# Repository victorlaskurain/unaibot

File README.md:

# Unaibot #

This project  is a  remote controller for  any robot  with independent
propulsion for the  left and right wheels: most  tricycle style robots
or any caterpillar robot, among others.

The code is currently being use to remotely control a robot build
around the
[Merkur Toys robot chassis 01](http://eshop.merkureducation.cz/show_product/?id=QuLuudfk8g).

I started  the project with a  double objective. In the  first place I
wanted  to  build a  remote  controlled  robot  for my  children.  The
secondary   objective  was   learning   a  little   bit  about   (AVR)
microcontroller programming. It's  been published in the  hope that it
will be  a good  starting point  for people sharing  any of  these two
goals.

## About this file ##

This file is expected  to be useful as a guide to  the code for anyone
willing to understand  how the whole setup works and  how to customize
it.

## How to build ##

The recommended  way to build  the project is  to execute make  in the
directory where the makefile is located.

```
make
```

This will create  a build directory alongside the  makefile which will
contain all the built files, both  the final binaries and the temporal
artifacts.

### About the build system ###

The  top  level  makefile  is a  non-recursive  makefile.   Using  the
utilities  provided by  the  top level  makefile  defining modules  is
straightforward.  A  module can  be  either  a  static library  or  an
executable:

Defining a module requires three steps:

1. Create a directory for the module, for example `registers`.
2. Put  the source files  in the directory. It  is advised to  put the
   header files in a a subdirectory lik `registers/include`.
3. Add   the   module.mk   module  definition   file,  in   this  case
   `registers/module.mk`.

All the  module definition files  are pretty much alike.  For example,
this is the module definition for the `registers` module:

```make
local_src  := $(wildcard $(src_subdirectory)/*.cpp)
$(call make-library, $(subdirectory)/libshift_register.a, $(local_src))
```

The first line stores  the list of all the source  files of the module
in  a  variable. `src_subdirectory`  is  a  handy make  function  that
returns the source directory.

The second line adds the  library `libshift_register.a` to the list of
libraries to  build.  Make  will use  the source  files listed  in the
variable `local_src`  to build the library.  `subdirectory` is similar
to `src_subdirectory` but  returns the build directory  instead of the
source directory.

The module  definition file for  an executable is very  similar. Let's
take for example the module definition of `robot_main`:

```make
local_src  := $(wildcard $(src_subdirectory)/*.cpp)
$(call make-program, $(subdirectory)/program, $(local_src), command/libcommand.a motor_driver/libmotor_driver.a pwm/libpwm.a shift_register/libshift_register.a serial/libserial.a)
```

As  you  can  see  the  only  noticeable  different  is  the  call  to
`make-program` instead  of `make-library` and the  fact that libraries
on which the program depends must be specified as third parameter.

## High level overview ##

The hardware setup is as follows:

- A smartphone is the remote controller.
- A Raspberry Pi together with an Arduino board make up the controller.
- The chassis is a Merku Toys robot chassis 01.
- Optionally the robot can stream what it sees through a webcam.

This components  form a stack and  communicate with each other  in the
following way:

- The chassis has two motors, one for the left caterpillar and one for
  the right caterpillar.
- The Arduino UNO board controls the motors with a Motor Shield v1 and
  reads commands from the serial port.
- A  Raspberry Pi sends commands  setting motor speeds to  the arduino
  using the serial port and serves  the web that implements the remote
  control.  It  gets remote  commands  through  a websocket.  It  also
  streams the webcam's video through a second websocket.
- The smartphone loads the remote control interface from the Raspberry
  pi, processes user  input and  sends commands  to the  Raspberry via
  websockets. It also renders the video stream if available.

The  user  interface running  on  the  smartphone  is plain  HTML  and
Javascript.

The  implementation of  the  web server  and the  server  side of  the
websockets is Nodejs based.

The code  running on the  Arduino uses the  AVR libraries but  not the
Arduino  libraries. The  reason not  to use  the Arduino  libraries is
twofold:

- Being very high  level and focused on being easy  to use for novices
  they  get in  the way  of  learning how  the microcontroller  really
  works.
- Although this is more a personal opinion rather than a fact based on
  rigorous measurements,  they are not  as type safe and  efficient as
  the might.

The following sections describe the  implementation details of each of
the aforementioned components.

# Motor control #

The motor driver implementation consists of several submodules:

- serial: implementation of a serial  port driver for the HW serial of
  the atmega328p.
- registers: type  safe interface to access the  hardware registers of
  the atmega328p.
- shift_register: implementation of a driver for a 74HCT595N IC.
- command:  implementation of  a command dispatcher.   robot_main uses
  this module to  parse and process the commands read  from the serial
  port  in an  organised  way  (currently there  is  a single  command
  defined so this is a bit of an overkill).
- pwm: implementation of the driver for the HW PWM of the atmega328p.
- motor\_driver: implementation  of a controller for  the Motor Shield
  v1. Uses the shift\_register module and the pwm module.
- robot_main: main   program,  uses serial,  command an  motor\_driver
  modules  and  implements  the   main  program  that  the  atmega328p
  executes.

## Serial port driver ##

### Quickstart ###

To use the serial just instantiate one of the available clases:

- `serial_9600`: unbuffered  read and write support at  9600 baud. All
  operations are synchronous, meaning that they take place in the main
  loop busy waiting as necessary.
- `serial_19200`:   unbuffered   read  and  write   support  at  19200
  baud. Same as the previous one, only faster.
- `serial_9600_async`: buffered  read and write support  at 9600 baud.
  All  operations are  asynchronous, meaning  that the  implementation
  uses interrupts. Reading  does not block as long as  the read buffer
  is not  empty. Conversely,  writing does  not block  as long  as the
  write buffer is not full.
- `serial_19200_async`:  buffered  read  and  write  support at  19200
  baud. Same as the previous one, only faster.

These are  just some of  the available  classes. There are  some other
options and more can be constructed on demand (see next section).

Async  versions   are  generally  more  efficient   but  require  more
memory. The memory requiremente derives  from the need to allocate the
buffers and the interruption handling routines.

In all cases parity and stop bits are the hardware's defaults.

The basic operations are:

- `inline uint8_t read()`: read one byte.
- `inline void write(const uint8_t byte)`: write one byte.

There are also versions to read and write whole buffers which could be
more efficient  than a plain  old loop.  There is  also a set  of free
function  templates which  are  the primary  public  interface to  the
serial port classes:

```c++
template <typename Serial>
uint8_t read(Serial &s);

template<typename Serial, typename SizeType>
inline SizeType read(Serial &s, uint8_t *buff, SizeType size);

template<typename Serial, typename SizeType>
inline SizeType read_line(Serial &s, uint8_t *buff, SizeType size,
                          uint8_t mark = '\n');

// write message and wait for enter key
template<typename serial_t>
void wait(serial_t &ser, const char* msg = 0);
```

### Implementation ###

The  serial  port  driver  is  a class  template  with  the  following
signature:

```c++
template<typename SerialSpeed,
         typename SerialReadMode,
         typename SerialWriteMode>
class serial : public SerialReadMode, public SerialWriteMode [...]
```

It  follows a  simple  policy  based design  where  each  of the  type
parameters represents a policy:

- `SerialSpeed`:  initialises the  serial port to  a given  baud rate,
  parity and stop  bit settings. The currently  available options only
  define different  baud rate  settings leaving  parity and  stop bits
  settings to the hardware's defaults.
- `SerialReadMode`: defines how to read bytes from the serial port. It
  can be set to `not_available` to instantiate a write only serial
  port. This could be useful to save some memory.
- `SerialWriteMode`: the  same   as `SerialReadMode`,  only for  write
  operations.

## Type safe and efficient register access ##

The atmega328p  presents all the  control registers and all  the input
and  output registers  mapped in  the memory  space. The  AVR avr/io.h
defines symbolic names for all  the registers as memory addresses. For
example, io.h defines the B io port  (PORTB) as 25h.  In turn the same
file defines each of this port's  bits as plain integers: PORTB0 is 0,
PORTB1 is 1, etc. This is not type safe, nothing prevents accidentally
mixing register PORTB with bit PORTC3, for example.

registers.hpp  defines  different  types  to  represent  each  of  the
registers uses the template class pin\_t to define different types for
each of the pins and tie  them to their respective register types. The
pin\_t template class defines a set  of functions to set and clear the
bits it represents in a safe way.

This is the interface of pin_t:

```c++
template <typename param_port_t, int pin_number>
struct pin_t
{
    typedef param_port_t port_t;
    inline static int offset();
    inline static void set();
    inline static void clear();
    inline static void set_mode_input();
    inline static void set_mode_output();
};
```

Using registers.hpp clearing the bit number 2 of PORTB turns from:

```
PORB &= ~_BV(PORTB2)
```

into the safer and more expressive:

```
PORTB2_t::clear();
```

The first  version is error  prone because if  we forget say  "~", the
compiler  won't complain  at  all  but the  result  won't  be the  one
expected. In other words, writing incorrect  code is very easy and the
compiler won't  help us.  With the  second option  the intent  is more
clear an writing wrong code is harder.

Moreover, the  implementation of  registers.hpp achieves this  with no
computational   cost.  Compiling   with  optimiseations   enabled  the
following two functions produce exactly the same assembler code:

```c++
uint8_t f1()
{
    PORTB |= _BV(PORTB0);
    PORTB &= ~_BV(PORTB0);
    return -1;
}

uint8_t f2()
{
    PORTB0_t::set();
    PORTB0_t::clear();
    return -1;
}
```

## Shift register driver ##

The  shift_register module  implements a  driver for  the the  74HC595
shift register integrated circuit. The API is a single template class:

```c++
template<typename shift_clk,
         typename store_clk,
         typename output_enable,
         typename ds,
         typename bit_field_t,
         size_t bit_field_size = 8 * sizeof(bit_field_t)>
struct shift_register
{
public:
    shift_register();
    ~shift_register();
    bit_field_t data;
    inline void commit(bit_field_t d)
    inline void commit() const
private:
    shift_register(const shift_register&)                  = delete;
    shift_register(shift_register&&)                       = delete;
    shift_register& operator=(const shift_register &other) = delete;
    shift_register& operator=(shift_register &&other)      = delete;
};

```

These are the template's parameters:

- shift\_clk: the  shift clock pin. A raising edge  in this pin shifts
  the existing bits of the shift register and stores a new bit.

- store\_clk:  the store clock pin.  A raising edge in  this ping puts
  the value of the value of the shift register into the store register
  (the parallel output).

- output_enable: if this pin is high then the output pins will assume
  the high impedance - OFF state.

- ds: the  rising edge of the  shift_clk takes the new  value from the
  value present at this pin.

- bit\_field\_t: the  data type used to represent in  memory the value
  of  the shift  register. Any  type should  be usable  as long  as it
  supports the binary and (&) and  shift bits left (<<) operations. In
  practice integer uint8_t has ever been used.

- bit\_field\_size: the number of  bits in bit\_field\_t. It takes the
  right value depending  on the size of bit\_field\_t, no  need to set
  it manually.

shift\_register expects the  pins to be represented  using an instance
of the  pin\_t described in the  previous section so an  example usage
would be the following:

```c++
#include <vla/shift_register.hpp>
#include <stdint.h>

using namespace vla;

int main(void) {
    // define de type and an instance
    shift_register<PORTD4_t/* arduino pin  4 */,
                   PORTB4_t/* arduino pin 12 */,
                   PORTD7_t/* arduino pin  7 */,
                   PORTB0_t/* arduino pin  8 */,
                   uint8_t> r;
    r.data = 0x81; // clear shift register
    r.commit();    // transfer the value to the parallel outuput
    while(true);   // shift register should show 0x81
}

```

## Command processor ##

The command processor  module provides a simple  framework to dispatch
command to handler  functions. In this context the  commands are plain
strings and the handlers have the following signature:

```c++
uint8_t operator()(const char* str)
```

The dispatcher calls each handler in order and until one of them
returns 0.

There is  no provision  to add handlers  dynamically, instead  all the
handlers   must    be   added   at    the   same   time    using   the
```make_command_dispatcher```  which  takes  any  number  of  callable
objects (functors, plain functions, ...) and returns a dispatcher:

```c++
template<typename ...Ts>
command_dispatcher<Ts...> make_command_dispatcher(const Ts&... args)
```

## PWD driver ##

### Quickstart ###

To  use  one of  the  4  PWD pins  supported  instantiate  one of  the
available classes:

-   ```pcpwm_portd6```,   ```pcpwm_portd5```,  ```pcpwm_portb3```   or
  ```pcpwm_portd3```.

For example:

```c++
// instantiate and configure timer
vla::timer0_pcpwm timer0;
timer0.set_clock(vla::clock_source::PRESCALE_1);
// set up PWM on pin d6
vla::pcpwm_portd6 pwm0a(timer0);
// set 50% duty cycle
pwm0a.set_level(UINT8_MAX / 2);
```

The implementation relays  on two templates.  In the  first place, the
```timer_configuration```  template  class   packs  together  the  two
registers used  to configure any  of the  two supported 8  bit timers.
For  example   the  ```timer0_pcpwm```  instantiation  helps   in  the
configuration of the 0 timer by binding together the two timer control
registers (```TCCR0A_t``` and ```TCCR0B_t```)  and the timer mode.  It
also  provides  a method  (```set_clock```)  to  change the  prescaler
(frequency) programmatically.

In  the second  place,  the  ```pwm``` template  class  binds a  timer
configuration  together with  the comparator  register and  the output
pin. This  class takes the  timer type  as template parameter  and the
timer instance  as constructor parameter.  The later's function  is to
ensure  that  the  user  doesn't  try to  use  a  PWM  output  without
configuring the timer first.

## Motor driver ##

This   module   is  an   driver   implementation   for  the   Adafruit
Motor/Stepper/Servo  Shield  for  Arduino.  The  shield  supports  two
stepper motors  or four DC  motors. This  driver supports only  the DC
motor configuration.

The shield uses a shift register  to set the turning direction of each
of the  four motors. The  implementation relays on the  shift register
module to  handle the shift  register and the  PWM module to  set each
motors power level.

The API is pretty straighforward:

```c++
class motor_driver
{
public:
    motor_driver();
    ~motor_driver();
public:
    motor0_t motor0;
    motor1_t motor1;
    motor2_t motor2;
    motor3_t motor3;
};
```

Once  instantiated  each of  the  four  motors  is available  via  the
corresponding  member  variable. The  type  of  each of  these  member
variables is an instantiation of  a class template. The class template
provides the  following public  member functions, which  hopefully are
self explanatory.

```c++
enum class direction_t : uint8_t
{
    IDLE      = 0x00,
    FORWARD   = 0x01,
    BACKWARD  = 0x02,
    STOP      = 0x11,
    FIRST     = IDLE,
    LAST      = STOP
};

void set_direction(direction_t d);
void set_speed(uint8_t s);
```

## Main program ##

The main program simply reads commands  from the serial port using the
serial port driver, parses them using the command dispatcher and sends
the corresponding lower  level commands to the motor  shield using the
motor driver.

```c++
int main()
{
    const auto CMD_BUFFER_SIZE = 64;
    uint8_t cmd_buffer[CMD_BUFFER_SIZE], err_code;
    serial_9600 ser;
    motor_driver motors;
    auto dispatch = make_command_dispatcher(set_speeds_cmd(motors));
    write_line(ser, "READY");
    while(true) {
        read_line(ser, cmd_buffer, CMD_BUFFER_SIZE, '\r');
        err_code = dispatch(reinterpret_cast<const char*>(&cmd_buffer[0]));
        if (SUCCESS == err_code) {
            write_line(ser, "OK");
        } else {
            write(ser, "ERROR ");
            write_line(ser, hex(err_code));
        }
    }
}
```

# Web based remote control #

The  web based  remote control  is  in the  web_control directory.   A
description  of  the  most  significant  contents  of  this  directory
follows:

- `bootstrap.sh`:   shell   script   to   install  all   the  required
  dependencies.

- `install.sh`:  shell script  to install the  remote controller  as a
  systemd service.  Copies  unaibot_web.js file and the  html, lib and
  node_modules  directories  into   `/opt/unaibot`  and  configures  a
  systemd service to run the the server.

- `lib/unaibot.js`:   it's  a   node   module.  Exports   the  UnaiBot
  constructor which takes as parameters the serial port and optionally
  its  configuration.  Instances of  this  object  provide high  level
  interface  for serial  port communication  between the  main program
  running  on the  Arduino  and the  world, in  this  case the  remote
  controller.

- `lib/botcam.js`: it's a node  module. Exports the BotCam constructor
  which takes as  paramenter the name of a video  device. Instances of
  this object provide the means  to start/stop the capture process and
  signal   the  activation/deactivation   of   the   camera  and   the
  availability of new captured frames.

- `unaibot_web.js`:  this is  the main program,  serves the  HTML page
  that  implements   the  remote's   GUI,  handles  the   server  side
  implementation of the remote's  commands and manages the websocket's
  server side.

## User interface ##

The user interface  is a multitouch web page which  shows two vertical
walls, one at each border.  The left war controls the left caterpillar
while the right  bar controls the right one. Pressing  on the top half
of the  bar lets  the caterpillar  run forward  while pressing  on the
bottom half lets it run backward. The round button at the center allow
activating and deactivating the camera.

A  couple  of Javascript  files  implement  touch event  handling  and
client/server communication.

- `api.js`: implementation of the client side of the protocol.

- `main.js`:  touch  event and  video  activation/deactivation   event
  handling.

## Remote API ##

At page  load the browsers opens  a connection to the  command socket.
Automatically reconnects if the connection breaks for any reason.

Two  types of  messages travel  through the  command socket.  The most
common are the requests and their  responses. The server can also send
asynchronous events to the browser.

There is a  second WebSocket endpoint handled by the  same node server
to stream the webcams video.

### Simple query / response protocol ###

The client  sends the request  and receives responses as  JSON encoded
Javascript objects.

The requests have the following properties:

- id: identifies  each request and must be unique  during the lifetime
  of a connection.

- type: identifies  the type of the message which  the server uses for
  message dispatching.

- data: if  the  messages requires  any  more  information  it can  be
  encoded in this property. The type field dictates the interpretation
  of this property.

The responses have the following properties:

- id: identifies each response, the value is equal to the value of the
  id field of the request to which this response answers.

- data:  the response data. The  type of the requests  dictates how to
  interpret this field and whether it is present at all.

### Asynchronous events ###

Asynchronous events  originate at  the server. The  server is  free to
send events  to the client  at any time.  The events are  JSON encoded
Javascript objects with the following properties:

- evt: a string with the event name. The client library triggers a DOM
  event to communicate the event to any interested listeners.

## Webcam streaming ##

[Jsmpeg](https://github.com/phoboslab/jsmpeg) provides  the Javascript
library to  render MPEG1 into a  canvas element. It also  provides the
necessary framework for  transmitting the vide frames  from the server
to the  client live using  websockets as transport. Although  it might
not be the most efficient codec the whole setup is very simple.

Client side, this three lines of Javascript direct the video player to
connect to the the given  websocket address start playback. The player
just sits there waiting for any video frames to render.

```javascript
var canvas = document.getElementById('video-canvas');
var url = 'ws://'+document.location.hostname+':8080/unaibot/cam';
var player = new JSMpeg.Player(url, {canvas: canvas});
```

Server side three different pieces of code work together to stream the
video.

On the first place the streaming process uses ffmpeg to initialize the
video  device,  capture raw  frames  and  encode  then in  the  format
required by Jsmpeg.

On the  second place there  is of course there  is the handler  of the
`/unaibot/cam` websocket endpoint.  Its  work is accepting connections
and broadcasting the video stream to all connected clients.

On the third place, the `botcam.js` module provides a simple interface
to the video capture device tailored to the needs of Jsmpeg. It how to
run ffmpeg encoder with the appropriate parameters. The module exports
a constructor (BotCam) whose instances have two public methods:

- capture(bool): activates the video  capture (true) or deactivates it
  (false).

- isVideoOn: returns true is the video capture is active.

and emit three events:

- videoOff:  notifies that the video  capture is off.  If  the library
  emits this event before the videoOn  event, then that means that the
  capture could not initialized for  whatever reason (no access to the
  device,  wrong ffmpeg  configuration or  any other  reason). If  the
  library emits this event after  a call to `capture(false)` it simply
  means that the capture shutdown process worked. The library can emit
  this event  at any other time,  which usually means that  the webcam
  got disconnected or for some reason the ffmpeg command died.

- videoOn: notifies that the video capture is on.

- data: when the video capture is  on the video data is made available
  to any interested listeners using  by emitting this event. The event
  object is  in the format required  by Jsmpeg so that  the web socket
  just needs to forward it to the remote clients.

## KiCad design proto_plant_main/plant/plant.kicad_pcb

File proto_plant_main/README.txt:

* PUBLIC ADDRESSES

|------------------------+-----------+---------+-----------+------------------------------------------------------------|
| Name                   | Block     | Address | Type      | Description                                                |
|------------------------+-----------+---------+-----------+------------------------------------------------------------|
| Line 1 bag counter     | Registers |    0x21 | [0,65535] |                                                            |
| Line 1 bag counter top | Registers |    0x36 | [0,65535] | if != 0, stop the line when the counter reaches this value |
| Line 1 bag weight      | Registers |    0x3a | [0,50000] | Real weight in gr. (simulated).                            |
| Line 1 bag weight ref  | Registers |    0x38 | [0,50000] | Weight reference in gr.                                    |
| Line 1 grinder control | Registers |    0x32 | [0,255]   | Grinder duty cycle. Only lowest byte meaningful.           |
| Line 1 grinder on      | Coils     |    0xc9 | [0,1]     | 1 if grinder is running. Read only.                        |
| Line 1 main switch     | Registers |    0x34 | [0,255]   | Only low byte used. If true, line is active.               |
| Line 1 oven power      | Registers |    0x30 | [0,3]     | Only two lowest bits are meaningful: off, 3: full power    |
| Line 2 bag counter     | Registers |    0x15 | [0,65535] |                                                            |
| Line 2 bag counter top | Registers |    0x37 | [0,65535] | if != 0, stop the line when the counter reaches this value |
| Line 2 bag weight      | Registers |    0x3b | [0,50000] | Real weight in gr. (simulated).                            |
| Line 2 bag weight ref  | Registers |    0x39 | [0,50000] | Weight reference in gr.                                    |
| Line 2 grinder control | Registers |    0x33 | [0,255]   | Grinder duty cycle. Only lowest byte meaningful.           |
| Line 2 grinder on      | Coils     |    0xca | [0,1]     | 1 if grinder is running. Read only.                        |
| Line 2 main switch     | Registers |    0x35 | [0,255]   | Only low byte used. If true, line is active.               |
| Line 2 oven power      | Registers |    0x31 | [0,3]     | Only two lowest bits are meaningful: off, 3: full power    |
| Silo level             | Registers |    0x00 | [0,1000]  | RO. Silo fill level. 0: empty, 1000: 100% full             |
|------------------------+-----------+---------+-----------+------------------------------------------------------------|

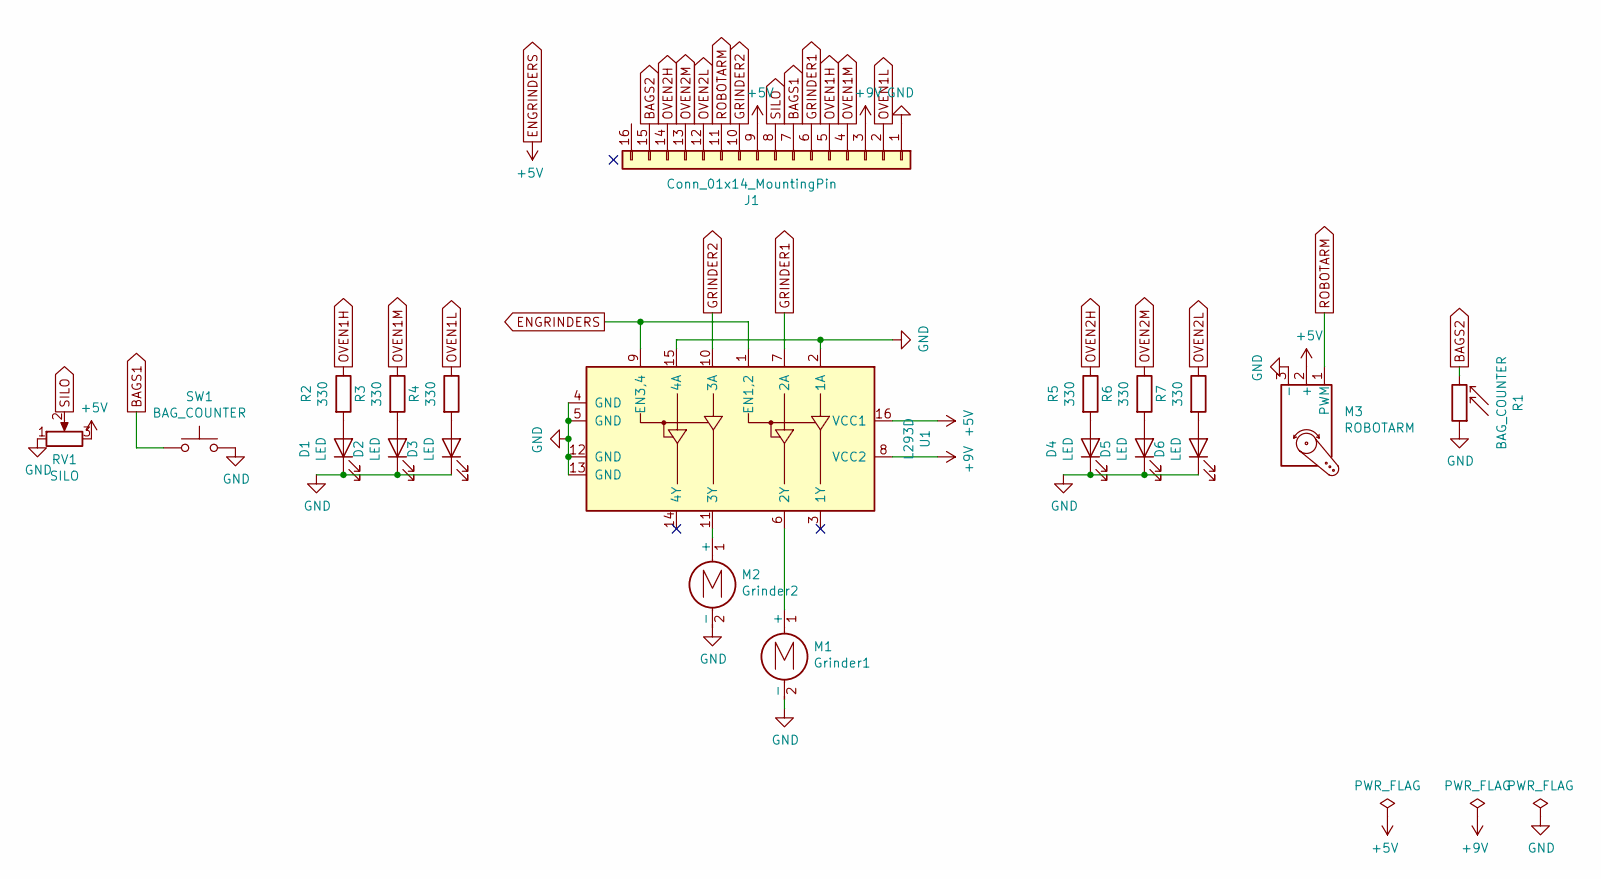
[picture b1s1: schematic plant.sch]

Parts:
D1, D2, D3, D4, D5, D6: LED; LED_D5.0mm
J1: Conn_01x14_MountingPin; PinSocket_1x16_P2.54mm_Vertical
M1: Grinder1; PinHeader_1x02_P2.54mm_Vertical
M2: Grinder2; PinHeader_1x02_P2.54mm_Vertical
M3: ROBOTARM; PinHeader_1x03_P2.54mm_Vertical
R1: BAG_COUNTER; R_LDR_4.9x4.2mm_P2.54mm_Vertical
R2, R3, R4, R5, R6, R7: 330; R_Axial_DIN0204_L3.6mm_D1.6mm_P5.08mm_Horizontal
RV1: SILO; Potentiometer_Bourns_3266Y_Vertical
SW1: BAG_COUNTER; SW_PUSH_6mm_H5mm
U1: L293D; DIP-16_W7.62mm

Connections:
+9V: J1.3, U1.8 (VCC2)
BAGS1: J1.7, SW1.1
BAGS2: J1.15, R1.2
ENGRINDERS: J1.9, M3.2 (+), RV1.3, U1.1 (EN1,2), U1.9 (EN3,4), U1.16 (VCC1)
GND: D1.1 (K), D2.1 (K), D3.1 (K), D4.1 (K), D5.1 (K), D6.1 (K), J1.1, M1.2 (-), M2.2 (-), M3.3 (-), R1.1, RV1.1, SW1.2, U1.2 (1A), U1.4 (GND), U1.5 (GND), U1.12 (GND), U1.13 (GND), U1.15 (4A)
GRINDER1: J1.6, U1.7 (2A)
GRINDER2: J1.10, U1.10 (3A)
unnamed: D1.2 (A), R2.2
unnamed: D2.2 (A), R3.2
unnamed: D3.2 (A), R4.2
unnamed: D4.2 (A), R5.2
unnamed: D5.2 (A), R6.2
unnamed: D6.2 (A), R7.2
unnamed: M1.1 (+), U1.6 (2Y)
unnamed: M2.1 (+), U1.11 (3Y)
OVEN1H: J1.5, R2.1
OVEN1L: J1.2, R4.1
OVEN1M: J1.4, R3.1
OVEN2H: J1.14, R5.1
OVEN2L: J1.12, R7.1
OVEN2M: J1.13, R6.1
ROBOTARM: J1.11, M3.1 (PWM)
SILO: J1.8, RV1.2

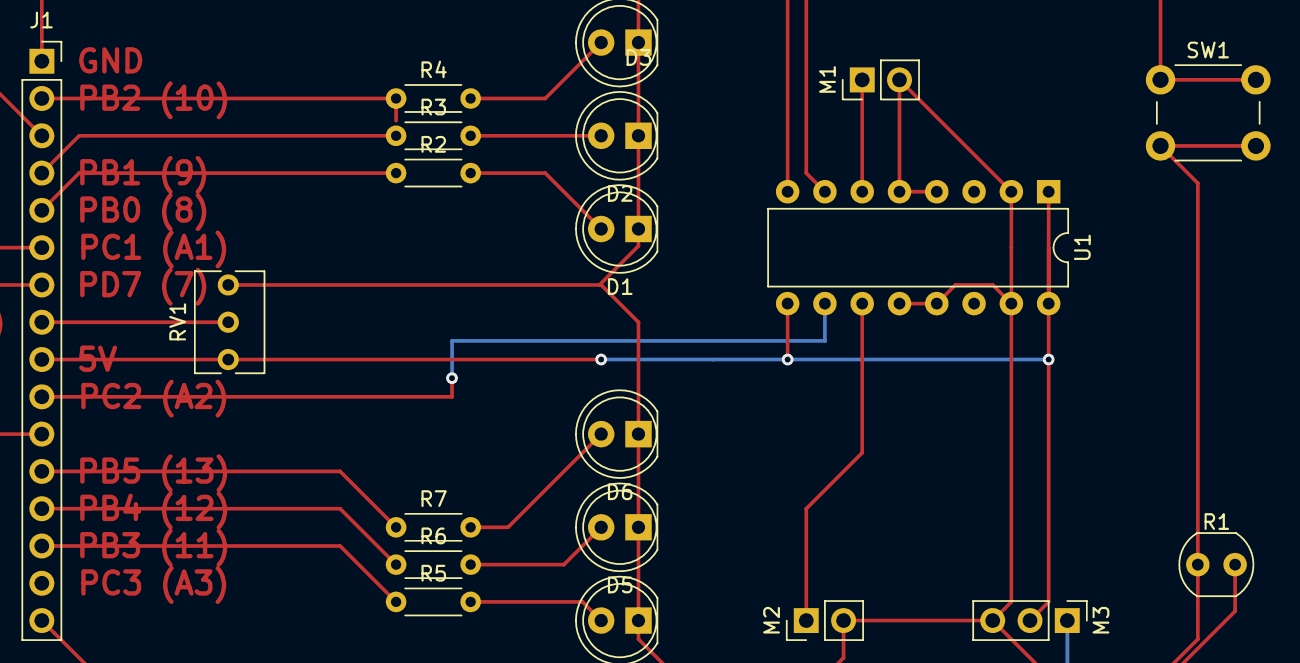
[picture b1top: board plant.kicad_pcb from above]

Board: 2 copper layers, 20 parts (0 on the bottom side), 23 nets.

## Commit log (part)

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2017-01-02 Initial revision.
2017-01-02 Add some comments. Clean up.
2017-01-03 Make less verbose.
2017-01-03 Add wrapper class for phase correct PWD.
2017-01-06 Fix includes.
2017-01-06 Fix comment.
2017-01-06 Add print-and-wait-for-key function for debugging.
2017-01-06 C++ register description.
    The registers module contains hardware register and pin definitions as
    an aid to implement higher level devices. For bit manipulation,
    compiling with optimizations enabled yields the same result as hand
    written bit operations.
2017-01-06 Add template to manage shift registers (74HC_HCT595).
    The test program is configured to switch the pins of the latch of an
    Arduino Motor Shield v1.
2017-01-08 Add compiler guards.
2017-01-08 Add Motor Shield v1 driver.
2017-01-09 Move .hpps to include directory. Use namespace for .hpps.
2017-01-10 Command distpatcher.
2017-01-11 Motor driver program with command dispatcher.
    The program reads commands from the serial line and programs the motor
    shield accordingly. Then reports success or error code back.
2017-01-12 Make STL optional.
2017-01-12 Fix include.
2017-01-12 Don't use strtol in order to save ~500 bytes.
    Reduces de uploaded binary size from 3070 to 2544 by reimplementing
    command parsing using a custom function which reads 0xXX numbers as
    uint8_t.
2017-01-17 Web interface for robot control.
2017-01-18 Extract communication with the arduino to the (new) unaibot module.
    This puts each responsibility where it belongs:
    - unaibot_web.js: handles HTTP and WS requests and dispatches then.
    - unaibot.js: handles serial communication with the arduino and
    provides a nice promise based protocol unaibot_web.
    Also make the serial handshake more solid.
2017-02-04 Systemd config file and install script for the web driver.
2017-02-05 Fix to load unaibot.service at boot.
2017-03-12 Add support for remote webcam.
2017-03-14 Fix visualization of camera feed.
    Change the order of the elements in the index.html to have them stack
    in the right order.
    Set maximum width and height to the canvas.
2017-03-14 Source ffmpeg configuration if needed.
2017-03-31 Extend the simple request/reply protocol with async events.
    Let the server send async messages (messages other than replies to
    requests) and handle them as events in the client.
    Use this channel to report camera status and set the camera toggle
    button's state accordingly.
2017-03-31 Do not indent first level of module content.
    No need to indent module contents just because they are in a closure.
2017-04-10 Use static member instead of lambda (untested).
    The lambda gets compiled two times into two identical versions in the
    final binary.
2017-04-13 Fix serial test.
    The delay gives time to the client program to start reading the serial
    port. Not using the lambda shaves 50 bytes from 1058 to 958 for
    serial_test/main.
2017-04-13 Support serial speeds up to 38400 bauds.
2017-06-01 Test serial write using base type as interface.
    The serial port configuration depends on its type but the read/write
    functions should not. This can be achieved now using the
    serial_async_read and serial_async_read classes for reading and the
    serial_async_write and serial_sync_write classes for writing.
2017-08-17 Get rid of STL dependency.
2017-08-17 Fill some gaps in the documentation.
2017-11-25 Driver for custom PCB motor driver.
2017-11-25 Support different arduino loaders via config files.
2017-11-26 Fix warning.
2019-02-22 Add some timer related registers.
2019-03-03 Set the correct baud rate for the UNO board.
2019-03-03 Add ADC related regiters.
2019-03-03 Add DIDR0 and PRR registers.
2019-03-03 Add submodule for zserge/pt.
2019-03-03 Add ADC driver.
2019-03-03 Add library to configure and use timers/counters.
2019-03-03 Distinguish between pin/bit and register/port.
    Let a port be one of the registers connected to the output pins. Let a
    pin be a bit of a register which is a port.
2019-03-03 Add C++ish protothread library.
    In particular implement a message queue including sincronization
    primitives so that the queue is useful in ISRs.
2019-03-03 Add ADLAR, ADPS0, ADPS1 and ADPS2 bits.
2019-03-03 Define SOURCE_DIR as the directory where the makefile is.
2019-03-03 Fix get and make offset constexpr.
    Fix the error and let offset be constexpr so that it can be used at
    compile time.
2019-03-03 Add test programs to generate simple tunes.
2019-03-03 Separate notes.cpp in three files to shave some bytes in the binary.
    Putting the find_closest_tc* function in different compilation units
    reduces de size of the buzzer_async_program from 2768 to 2074.
    Also let the clock_source_* types used match the corresponding
    find_closest_tc* functions as they should.
2019-03-04 Make makefile less verbose by default and fix messages.
2019-03-10 Allow device selection using a parameter. Add usage message.
2019-03-10 Allow specifying the build directory in the command line.
    Call make BUILD_DIR=xxx to build into the directory xxx. The default
    value for BUILD_DIR is build.
    Create the build directory as needed.
2019-03-10 Force recompilation if makefile or module.mk changes.
2019-03-10 Simplify the usage of library and program creation functions.
    Put the eval call that was required to create a library or a program
    inside the make-program/make-library definition instead of in the call
    site.
2019-03-10 Include list of available targets in the usage message.
2019-03-10 Add classes to generate clock ticks at 20Khz handle alarms.
2019-03-23 Improve msg_queue.
    - Make the full capacity of the queue available to the user.
    - Let the user decide if either the read lock or the write (or both)
    is required. For example, if all the push calls take place inside an
    interruption handler, there is no need for any locks since the
    operations will run atomically at any rate.
    - Make the msg_queue more easily extendable.
2019-03-23 Make a more C++ish API for protothreads.
2019-03-23 Check short timeouts.
2019-03-23 Refactor serial port class.
    Do not use speed as template parameter, instead let the serial speed
    be a parameter to the constructor.
    Add parameters to the constructor and a configuration function to
    configure the serial port parameters safely.
    Refactor serial port.
2019-03-30 Support using the general digital I/O pins for input.
2019-03-30 PDU test.
2019-04-18 Add binary input debouncing library and sample program.
2019-04-19 Set mode and activate deactive pull ups at the port level.
2019-04-19 Remove unused member variable.
2019-04-19 Use 2 counters in the debouncer sample program.
2019-04-19 Fix definition of msg_queue::_full.
2019-04-19 Remove circular_buffer and use instead msg_queue for the serial library.
    The aim is to reduce code duplication by using the
    safer/simpler/better tested msg_queue in place of the custom
    circular_buffer.
2019-04-19 Remove unused compiler flag.
2019-04-19 Add support for higher baud rates.
2019-04-20 Use max baud rate and async serial driver.
2019-04-25 Rename pdu_test to modbus_rtu_slave and organize code in files.
2019-04-29 Implement RTU Write Single Coil and Write Coils skeleton.
2019-04-29 Use 19200 baud as default.
2019-05-12 Implement RTU Read Holding Registers skeleton.
2019-05-12 Implement RTU Write Registers/RTU Write Single Register skeleton.
2019-05-12 Add write_coils based default implementation for write_single_coil.
2019-05-12 Implement RTU Read Coils skeleton.
2019-05-12 Fix race condition.
    If the time required to process the frame was longer than the
    remaining wait time, in other words, if the timeout message arrived
    before the buffer the transmission handler would get stuck in the
    PROCESSING state.
2019-05-18 Simplify RTU data model and begin read coils implementation.
2019-05-19 Implement ADC access (initial version).
    Add a daemon to read analog data without blocking the rest of the
    processes. Add queue based communication between the pdu_handler and
    the adc daemon.
2019-05-19 Fix set_mode_input.
2019-05-19 Implement RTU Write Registers based on Write Single Register.
2019-05-26 Fix documentation.
2019-05-26 Fix definition of AU bits.
2019-05-31 Fixes on adc daemon and on pdu_handler <-> adc daemon communication.
2019-05-31 Add curses based client to read and write MODBUS coils.
    Add a custom curses based client to read and edit the values of all
    the coils of the modbus server.
2019-06-01 Mark PC6 as unavailable.
2019-06-10 Implement writing registers from the tui client.
2019-06-12 Base read_registers on read_single_register. Same for writting.
    Initial implementation of analog write.
2019-06-12 Implement inc/dec registers in tui client.
2019-06-12 Implement PD3 PWM output mode.
2019-06-13 Implement PB3 PWM output mode.
2019-06-14 Put TC config message parsing and generation in utility class.
2019-06-14 Let TC2 instances be members like the rest of the elements.
2019-06-22 Refactor message queues using new safe union template class.
    Use the reusable tagged_union and tagged_union_queue templates to
    implement the message queues that must deliver several message types
    instead of the old hand crafted implementations.
    This reduces code duplication and makes extending the set of messages
    supported by a queue trivial.
2019-06-24 Order counters using the same order as the PDU handler.
2019-06-24 Make protothreads moveable and not copyable
2019-06-26 Order ports lexicographically in the MODBUS address space.
    PORTB, then PORTC and then PORTD for all coils, counters, etc.
2019-06-26 Tag counter names with the corresponding port/pin number.
2019-06-26 Support 24 counters in TUI client.
2019-06-26 Group together some related constants.
2019-07-14 Record max run-time for the whole main loop. Publish as user data.
2019-07-14 Add missing parameter to support local statics variables.
    This should have been added in commit c0c35b but was left out
    accidentally.
2019-07-14 Show more tables in TUI client.
2019-07-14 Document timing issues.
2019-07-21 Use message_with_reply to simplify the implementation of the counter daemon.
    Use the message_with_reply utility class to define counter_msg_t
    message which requires a reply in the specified queue in a cleaner and
    more generic way.
2019-07-21 Add the message_with_reply utility template class.
    This class provides a way to define type safe request/reply messages
    more convenient and generic.
2019-07-21 Use message_with_reply to simplify the implementation of the adc daemon.
    Use the message_with_reply utility class to define adc_msg_t message
    which requires a reply in the specified queue in a cleaner and more
    generic way.
2019-07-22 Implement commands to store and load port configuration.
2019-09-20 Support both serial port and TCP servers.
2019-12-01 Add main program for plant prototype controller.
2019-12-01 Add missing files.
2019-12-01 make execute_{write,read}_single_{coil,register} public.
    This functions will be useful for the implementation of custom RTU
    slaves.
2019-12-01 modbus_rtu_slave: separate main from the rest of the source files.
    Put the rest of the source files in a reusable library.
2019-12-06 Add utility function to set a registry with a mask.
2019-12-06 Implement oven control.
2019-12-06 Add TUI with support for the app specific user data records.
2019-12-07 Implement grinder control and photoresistor counter.
2019-12-07 Implement a main switch for each line.
2019-12-07 Document public Modbus addresses.
2019-12-07 Add Kicad diagrams.
2019-12-30 Allow stopping and starting the program through Modbus.
    The program imposes certain restrictions on the standing values of the
    outputs. Deactivating the programs makes it possible to set any output
    signal to any desired value for testing or other purposes.
